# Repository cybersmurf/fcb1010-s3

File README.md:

# FCB1010-S3

Upgrade old fcb1010 to new era.

Přestavba nožního MIDI ovladače Behringer FCB1010 na ESP32-S3: původní hlavní deska a síťový zdroj ven, místo nich vlastní nosná deska s ESP32-S3-DevKitC-1.

*Rebuild of the Behringer FCB1010 MIDI foot controller around an ESP32-S3 (USB MIDI, 5-pin DIN MIDI, device profiles). Documentation is in Czech.*

## Co má umět

- **Ovladač DAW přes USB** (Logic Pro): transport, undo, cycle, metronom, pedály. USB MIDI bez ovladačů, napájení jedním kabelem USB-C.
- **Samostatný ovladač přes 5pinové MIDI**, hlavně pro Boss GX-700: volba patchů, pedály.
- **MIDI rozhraní USB ↔ DIN** pro počítač.
- Profily jako sestavy: jeden pedál může poslat více zpráv více přístrojům.
- Možnosti dalšího rozvoje: NUX MG-30 (jack TRS, USB host), Mackie Control s LED zpětnou vazbou, další profily.

## Stav (16. 11. 2026)

| Část | Stav |
|---|---|
| Koncepce a specifikace | hotová, verze 2 |
| Pinout a bloky nosné desky | verze 0.2, konektory předních desek neověřené |
| Firmware | verze 0.1: USB MIDI, 12 spínačů, 2 pedály, WS2812B. Sestaví se, **na hardwaru zatím neběžel** |
| Automatické kontroly | u každého pull requestu se pustí testy logiky a sestaví firmware |
| Měření vlastního kusu | čeká na otevření přístroje |
| Schéma a deska (KiCad) | nezačato |

## Obsah

| Cesta | Co tam je |
|---|---|
| [`docs/specifikace.md`](docs/specifikace.md) | co má přístroj umět, profily, směrování MIDI, stavba firmwaru, postup, rizika |
| [`docs/pinout.md`](docs/pinout.md) | přiřazení GPIO, konektory, bloky desky, displej |
| [`docs/obvody.md`](docs/obvody.md) | zapojení vstupů pedálů a spínačů, filtry, napájení, zem |
| [`docs/mereni.md`](docs/mereni.md) | měřicí protokol pro otevření přístroje |
| [`docs/nalezy-z-fotek.md`](docs/nalezy-z-fotek.md) | co je vidět na fotkách otevřeného přístroje (18. 11. 2026) |
| [`hardware/`](hardware/) | rozvržení nosné desky, schéma v PDF a [`hardware/kicad/`](hardware/kicad/) se schématem pro KiCad |
| [`docs/nakup.md`](docs/nakup.md) | nákupní seznam |
| [`docs/navrh.md`](docs/navrh.md) | první verze návrhu, co víme o vnitřku FCB, checklist měření |
| [`docs/pruzkum-vnitrni-zapojeni.md`](docs/pruzkum-vnitrni-zapojeni.md) | průzkum vnitřního zapojení FCB1010 s citacemi a mírou jistoty |
| [`docs/zdroje.md`](docs/zdroje.md) | všechny použité zdroje s výtahy |
| [`firmware/`](firmware/) | projekt pro PlatformIO (arduino-esp32 3.x) |

## Sestavení firmwaru

```
cd firmware
pio run
pio run -t upload
```

Podrobnosti v [`firmware/README.md`](firmware/README.md).

## Upozornění

- Uvnitř původního FCB1010 je síťové napětí. Měření za chodu jen s rozmyslem.
- Pinouty konektorů v dokumentaci pocházejí z cizích kusů a z fór. Před zapojením ověřit na vlastním přístroji.
- Licence zatím není určená.

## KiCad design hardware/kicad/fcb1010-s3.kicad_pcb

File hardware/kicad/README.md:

# Schéma nosné desky (KiCad)

| Soubor | Co to je |
|---|---|
| `fcb1010-s3.kicad_sch`, `fcb1010-s3.kicad_pro` | schéma, otevře se v KiCadu 7 a novějším |
| `gen_sch.py` | generátor schématu; zapojení je popsané v něm a schéma se z něj vyrábí |
| `expected-nets.json` | zamýšlené přiřazení pin → síť, vzniká při generování |
| `check_netlist.py` | porovná netlist vyexportovaný KiCadem se zamýšleným zapojením |
| `../schema-fcb1010-s3.pdf` | schéma v PDF |
| `gen_pcb.py` | generátor desky: rozmístění součástek a sítě; spouští se `/usr/bin/python3 gen_pcb.py` (potřebuje modul `pcbnew` z KiCadu) |
| `fcb1010-s3.kicad_pcb` | deska 229 × 41 mm, dvouvrstvá, součástky rozmístěné a spoje natažené autorouterem |
| `import_ses.py` | načte výsledek autorouteru Freerouting (`.ses`) do desky |
| `check_pcb.py` | nezávislá kontrola, že jsou v každé síti všechny pájecí body propojené |
| `../deska-fcb1010-s3.pdf`, `../deska-horni-strana.png`, `../deska-spodni-strana.png` | deska se spoji a obrázky obou stran |
| `../fcb1010-s3-gerber-v0.3.zip` | gerbery a vrtání pro výrobu |
| `fcb1010.pretty/` | vlastní pouzdra: DevKit 2×22 a úhelník |
| `parts.json` | seznam součástek (hodnota, pouzdro), vzniká při generování schématu |
| `../deska-rozmisteni.png` | obrázek rozmístění |

Postup po změně zapojení:

```
python3 gen_sch.py
kicad-cli sch export netlist -o fcb1010-s3.net fcb1010-s3.kicad_sch
python3 check_netlist.py fcb1010-s3.net
kicad-cli sch export pdf -o ../schema-fcb1010-s3.pdf fcb1010-s3.kicad_sch
```

Schéma se neupravuje ručně v editoru, jinak ho další generování přepíše.

## Stav (v0.1, 18. 11. 2026)

- Kontrola netlistu: 310 pinů, 90 sítí, bez rozdílů proti zadání.
- **Ověřeno z fotek (24. 11. 2026):** zapojení 14pinových svazků J1 a J2 (společný vodič, UP/DOWN, krajní spínač, napájení LED; pořadí prostředních pinů jednotlivě ne, dá se přemapovat ve firmwaru), rozložení pinů DevKitu a rozteč jeho řad 25,4 mm. Viz `docs/nalezy-z-fotek.md`.
- Orientace diod u spínačů: z fotek vychází společný vodič na GND a pull-up, tedy JP1 i JP2 v poloze A; při oživení ověřit.
- **Neověřeno:** pořadí vodičů pedálů J3 a J4, pořadí pinů modulu OLED (J5).
- Propojky JP1 a JP2 dovolují obrátit polaritu čtení spínačů, kdyby diody na předních deskách byly orientované opačně.
- U4 (MCP1702-4002E/TO, 4,0 V) je volitelný; bez něj se spojí JP3 a senzory pedálů se napájejí z 5 V přes R24 a C5.
- Deska: součástky jsou rozmístěné bez překryvů (kontrola v `gen_pcb.py`). Spoje natáhl Freerouting 1.9.0: 1326 segmentů, 61 prokovů, 7,5 m spojů. Signály 0,3 mm, GND a +5 V 0,6 mm, +3V3 a napájení senzorů 0,4 mm (s 0,6 mm se nedalo natáhnout). Izolační mezera 0,2 mm, spoje nejméně 0,6 mm od hrany desky. Na obou vrstvách je rozlitá zem.
- Kontroly (24. 11. 2026): KiCad i `check_pcb.py` hlásí 0 nepropojených spojení (90 sítí). Kontrola návrhových pravidel KiCadu (`drc.rpt`, pouští ji `import_ses.py`) nenašla žádný zkrat, porušení izolační mezery ani vzdálenosti od hrany. Zbývají jen upozornění: překryvy potisku, 2 zemní body připojených k rozlité zemi jedním můstkem místo dvou (jsou připojené i spojem).
- Konektory svazků J1 až J4 mají pin 1 (červený vodič) na konci dál od displeje, stejně jako původní deska (fotka IMG_9456). J1 je blíž k displeji a patří ke spodní desce spínačů (1–5, DOWN), J2 k horní (6–10, UP), viz `docs/nalezy-z-fotek.md`.
- Popisky konektorů jsou na potisku.
- Výrobní podklady: `../fcb1010-s3-gerber-v0.3.zip` (gerbery a vrtání, 2 vrstvy, 229 × 41 mm, tloušťka 1,6 mm). Oválné otvory úhelníků jsou prokovené drážky 1,3 × 2,1 mm.
- Polohy konektorů na hraně jsou podle fotek strany součástek s metrem zaháknutým za hranu desky (24. 11. 2026): pin 1 konektoru J1 na 40,3 mm, J2 74,3 mm, J4 89,0 mm, J3 100,5 mm, J7 (X18) 137,0 mm, J11 (X17) 210,3 mm od hrany u displeje; přesnost asi ±2 mm, u X17 a X18 ±3 mm. Lišty X17 a X18 mají rozteč 2,0 mm, J7 a J11 jsou proto obyčejné řady 1×4 s roztečí 2,0 mm, do kterých se dají přepájet původní lišty s límcem. Pin 1 (červený vodič) je u všech na konci dál od displeje; u X17 a X18 je to odvozené z potisku a ostatních konektorů, při pájení ověřit podle červeného vodiče.
- **Pod DevKitem není žádná součástka (v0.3, 24. 11. 2026).** JP1 a JP2 jsou nad budičem U3, JP3 u stabilizátoru senzorů, JP4 a J9 na konci desky u výstupů, odpory R18 až R23 a kondenzátory C3, C4 ve dvou řadách mezi DevKitem a hranou se svazky. Kontrola v `gen_pcb.py` hlídá i překryv s DevKitem.
- Displej na desce není: připojuje se čtyřpinovým konektorem J5 a jeho držák se vyřeší podle skutečného modulu.
- Deska je připravená k objednání prototypu. Zbylé neověřené body se dají vyřešit při osazování (pořadí vodičů při pájení, propojky, firmware).

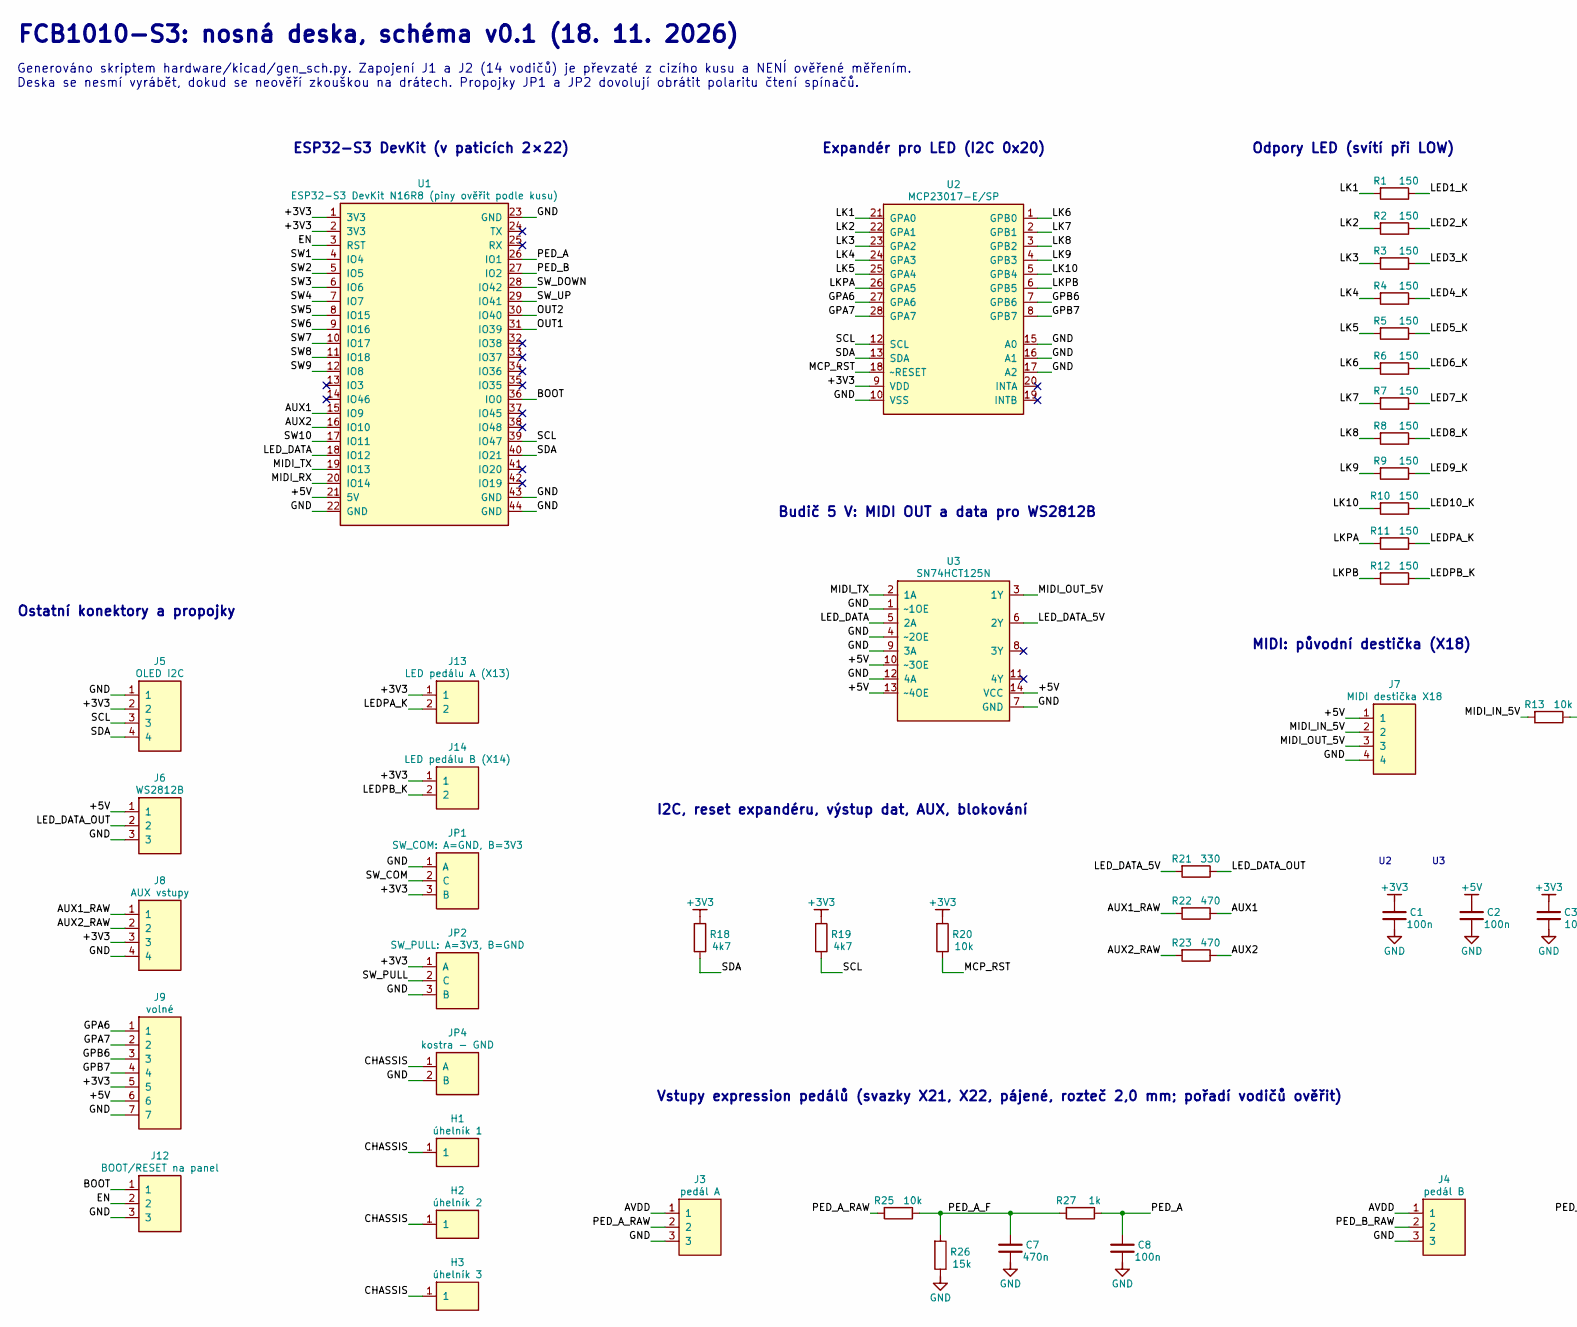
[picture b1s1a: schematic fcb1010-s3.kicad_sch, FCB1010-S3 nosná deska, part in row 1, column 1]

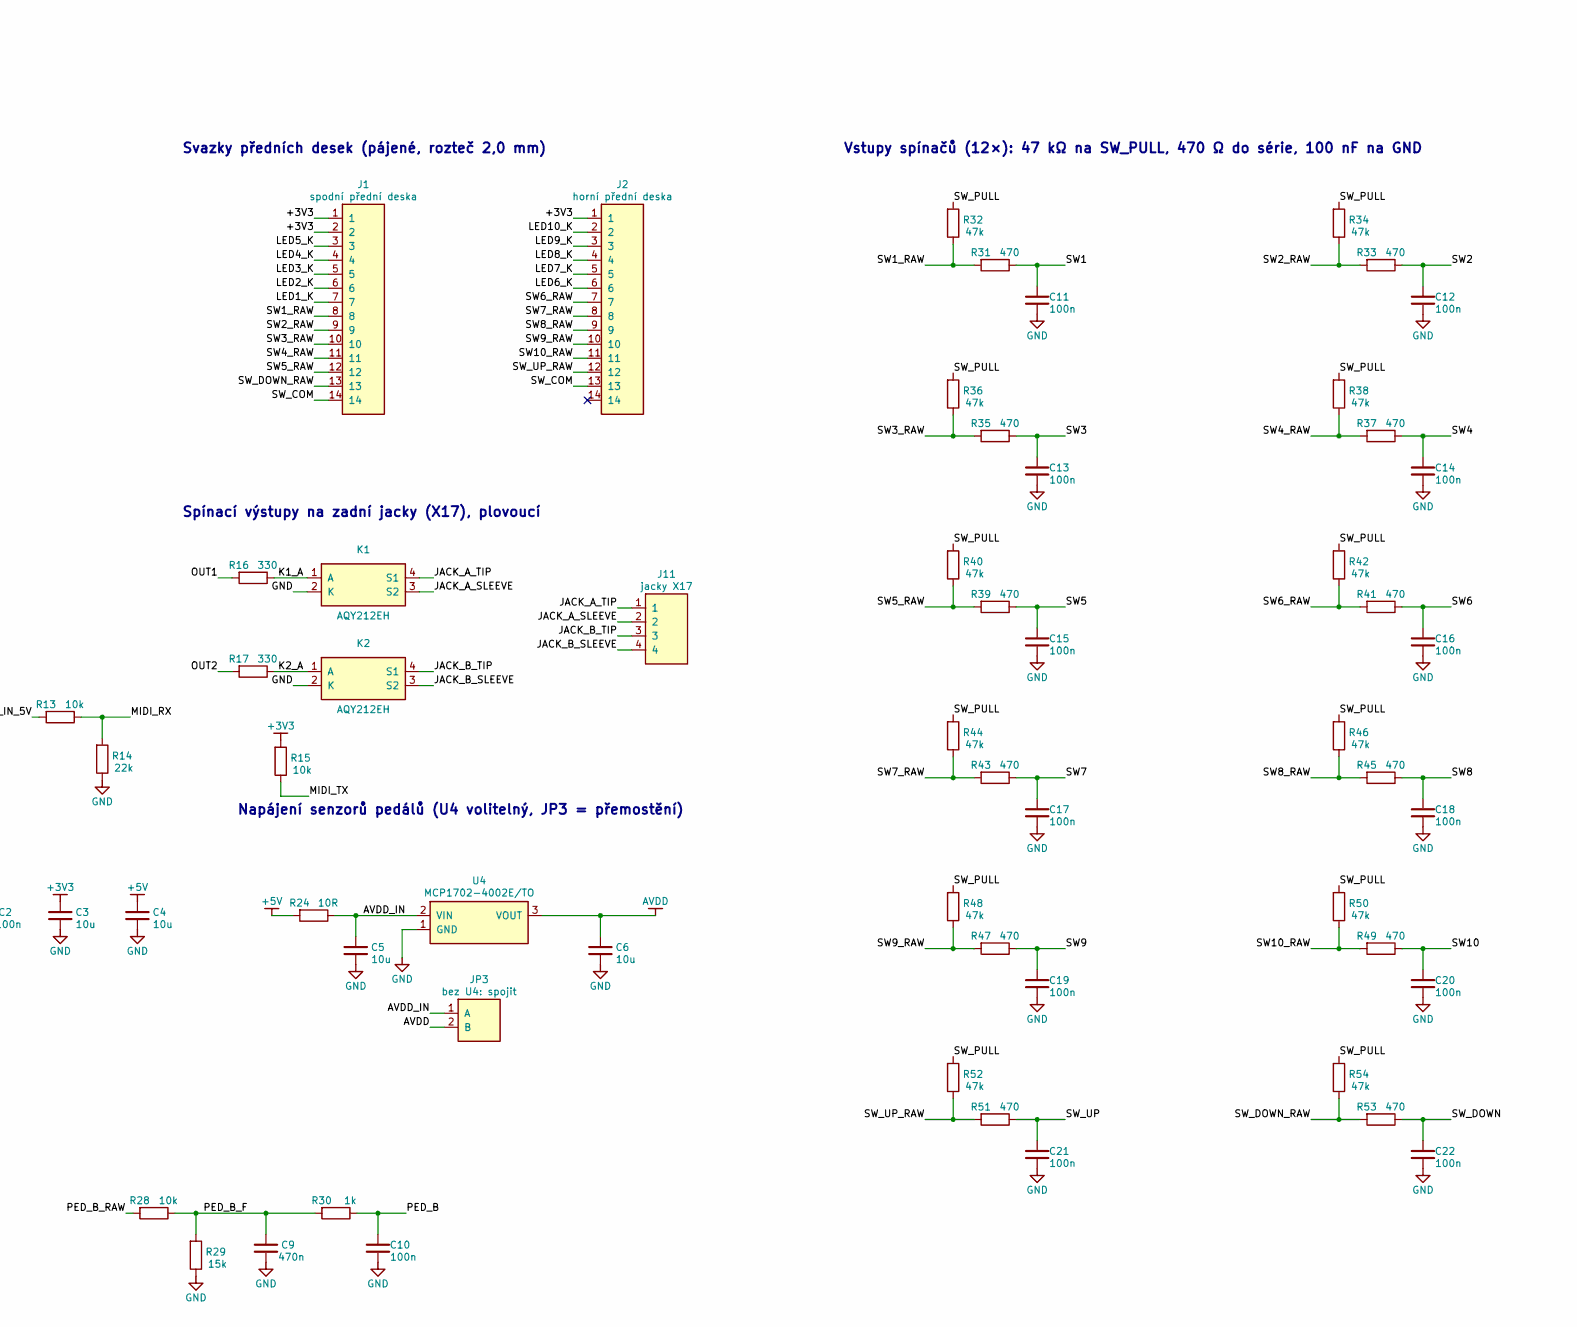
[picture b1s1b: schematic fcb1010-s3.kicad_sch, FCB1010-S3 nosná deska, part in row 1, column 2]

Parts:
C1, C2, C8, C10, C11, C12, C13, C14, C15, C16, C17, C18, C19, C20, C21, C22: 100n; C_Disc_D5.0mm_W2.5mm_P5.00mm
C3, C4, C5, C6: 10u; C_Disc_D5.0mm_W2.5mm_P5.00mm
C7, C9: 470n; C_Disc_D5.0mm_W2.5mm_P5.00mm
H1: úhelník 1; Uhelnik
H2: úhelník 2; Uhelnik
H3: úhelník 3; Uhelnik
J1: spodní přední deska; PinHeader_1x14_P2.00mm_Vertical
J2: horní přední deska; PinHeader_1x14_P2.00mm_Vertical
J3: pedál A; PinHeader_1x03_P2.00mm_Vertical
J4: pedál B; PinHeader_1x03_P2.00mm_Vertical
J5: OLED I2C; PinHeader_1x04_P2.54mm_Vertical
J6: WS2812B; PinHeader_1x03_P2.54mm_Vertical
J7: MIDI destička X18; PinHeader_1x04_P2.00mm_Vertical
J8: AUX vstupy; PinHeader_1x04_P2.54mm_Vertical
J9: volné; PinHeader_1x07_P2.54mm_Vertical
J11: jacky X17; PinHeader_1x04_P2.00mm_Vertical
J12: BOOT/RESET na panel; PinHeader_1x03_P2.54mm_Vertical
J13: LED pedálu A (X13); PinHeader_1x02_P2.00mm_Vertical
J14: LED pedálu B (X14); PinHeader_1x02_P2.00mm_Vertical
JP1: SW_COM: A=GND, B=3V3; PinHeader_1x03_P2.54mm_Vertical
JP2: SW_PULL: A=3V3, B=GND; PinHeader_1x03_P2.54mm_Vertical
JP3: bez U4: spojit; PinHeader_1x02_P2.54mm_Vertical
JP4: kostra - GND; PinHeader_1x02_P2.54mm_Vertical
K1, K2: AQY212EH; DIP-4_W7.62mm
R1, R2, R3, R4, R5, R6, R7, R8, R9, R10, R11, R12: 150; R_Axial_DIN0207_L6.3mm_D2.5mm_P10.16mm_Horizontal
R13, R15, R20, R25, R28: 10k; R_Axial_DIN0207_L6.3mm_D2.5mm_P10.16mm_Horizontal
R14: 22k; R_Axial_DIN0207_L6.3mm_D2.5mm_P10.16mm_Horizontal
R16, R17, R21: 330; R_Axial_DIN0207_L6.3mm_D2.5mm_P10.16mm_Horizontal
R18, R19: 4k7; R_Axial_DIN0207_L6.3mm_D2.5mm_P10.16mm_Horizontal
R22, R23, R31, R33, R35, R37, R39, R41, R43, R45, R47, R49, R51, R53: 470; R_Axial_DIN0207_L6.3mm_D2.5mm_P10.16mm_Horizontal
R24: 10R; R_Axial_DIN0207_L6.3mm_D2.5mm_P10.16mm_Horizontal
R26, R29: 15k; R_Axial_DIN0207_L6.3mm_D2.5mm_P10.16mm_Horizontal
R27, R30: 1k; R_Axial_DIN0207_L6.3mm_D2.5mm_P10.16mm_Horizontal
R32, R34, R36, R38, R40, R42, R44, R46, R48, R50, R52, R54: 47k; R_Axial_DIN0207_L6.3mm_D2.5mm_P10.16mm_Horizontal
U1: ESP32-S3 DevKit N16R8 (piny ověřit podle kusu); ESP32-S3-DevKit_2x22_RM25.4mm
U2: MCP23017-E/SP; DIP-28_W7.62mm_Socket
U3: SN74HCT125N; DIP-14_W7.62mm_Socket
U4: MCP1702-4002E/TO; TO-92_Inline

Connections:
+3V3: C1.1, C3.1, J1.1, J1.2, J2.1, J5.2, J8.3, J9.5, J13.1, J14.1, JP1.3 (B), JP2.1 (A), R15.1, R18.1, R19.1, R20.1, U1.1 (3V3), U1.2 (3V3), U2.9 (VDD)
+5V: C2.1, C4.1, J6.1, J7.1, J9.6, R24.1, U1.21 (5V), U3.10 (~3OE), U3.13 (~4OE), U3.14 (VCC)
AUX1: R22.2, U1.15 (IO9)
AUX1_RAW: J8.1, R22.1
AUX2: R23.2, U1.16 (IO10)
AUX2_RAW: J8.2, R23.1
AVDD: C6.1, J3.1, J4.1, JP3.2 (B), U4.3 (VOUT)
AVDD_IN: C5.1, JP3.1 (A), R24.2, U4.2 (VIN)
BOOT: J12.1, U1.36 (IO0)
CHASSIS: H1.1, H2.1, H3.1, JP4.1 (A)
EN: J12.2, U1.3 (RST)
GND: C1.2, C2.2, C3.2, C4.2, C5.2, C6.2, C7.2, C8.2, C9.2, C10.2, C11.2, C12.2, C13.2, C14.2, C15.2, C16.2, C17.2, C18.2, C19.2, C20.2, C21.2, C22.2, J3.3, J4.3, J5.1, J6.3, J7.4, J8.4, J9.7, J12.3, JP1.1 (A), JP2.3 (B), JP4.2 (B), K1.2 (K), K2.2 (K), R14.2, R26.2, R29.2, U1.22 (GND), U1.23 (GND), U1.43 (GND), U1.44 (GND), U2.10 (VSS), U2.15 (A0), U2.16 (A1), U2.17 (A2), U3.1 (~1OE), U3.4 (~2OE), U3.7 (GND), U3.9 (3A), U3.12 (4A), U4.1 (GND)
GPA6: J9.1, U2.27 (GPA6)
GPA7: J9.2, U2.28 (GPA7)
GPB6: J9.3, U2.7 (GPB6)
GPB7: J9.4, U2.8 (GPB7)
JACK_A_SLEEVE: J11.2, K1.3 (S2)
JACK_A_TIP: J11.1, K1.4 (S1)
JACK_B_SLEEVE: J11.4, K2.3 (S2)
JACK_B_TIP: J11.3, K2.4 (S1)
K1_A: K1.1 (A), R16.2
K2_A: K2.1 (A), R17.2
LED1_K: J1.7, R1.2
LED2_K: J1.6, R2.2
LED3_K: J1.5, R3.2
LED4_K: J1.4, R4.2
LED5_K: J1.3, R5.2
LED6_K: J2.6, R6.2
LED7_K: J2.5, R7.2
LED8_K: J2.4, R8.2
LED9_K: J2.3, R9.2
LED10_K: J2.2, R10.2
LEDPA_K: J13.2, R11.2
LEDPB_K: J14.2, R12.2
LED_DATA: U1.18 (IO12), U3.5 (2A)
LED_DATA_5V: R21.1, U3.6 (2Y)
LED_DATA_OUT: J6.2, R21.2
LK1: R1.1, U2.21 (GPA0)
LK2: R2.1, U2.22 (GPA1)
LK3: R3.1, U2.23 (GPA2)
LK4: R4.1, U2.24 (GPA3)
LK5: R5.1, U2.25 (GPA4)
LK6: R6.1, U2.1 (GPB0)
LK7: R7.1, U2.2 (GPB1)
LK8: R8.1, U2.3 (GPB2)
LK9: R9.1, U2.4 (GPB3)
LK10: R10.1, U2.5 (GPB4)
LKPA: R11.1, U2.26 (GPA5)
LKPB: R12.1, U2.6 (GPB5)
MCP_RST: R20.2, U2.18 (~RESET)
MIDI_IN_5V: J7.2, R13.1
MIDI_OUT_5V: J7.3, U3.3 (1Y)
MIDI_RX: R13.2, R14.1, U1.20 (IO14)
MIDI_TX: R15.2, U1.19 (IO13), U3.2 (1A)
OUT1: R16.1, U1.31 (IO39)
OUT2: R17.1, U1.30 (IO40)
PED_A: C8.1, R27.2, U1.26 (IO1)
PED_A_F: C7.1, R25.2, R26.1, R27.1
PED_A_RAW: J3.2, R25.1
PED_B: C10.1, R30.2, U1.27 (IO2)
PED_B_F: C9.1, R28.2, R29.1, R30.1
PED_B_RAW: J4.2, R28.1
SCL: J5.3, R19.2, U1.39 (IO47), U2.12 (SCL)
SDA: J5.4, R18.2, U1.40 (IO21), U2.13 (SDA)
SW1: C11.1, R31.2, U1.4 (IO4)
SW1_RAW: J1.8, R31.1, R32.2
SW2: C12.1, R33.2, U1.5 (IO5)
SW2_RAW: J1.9, R33.1, R34.2
SW3: C13.1, R35.2, U1.6 (IO6)
SW3_RAW: J1.10, R35.1, R36.2
SW4: C14.1, R37.2, U1.7 (IO7)
SW4_RAW: J1.11, R37.1, R38.2
SW5: C15.1, R39.2, U1.8 (IO15)
SW5_RAW: J1.12, R39.1, R40.2
SW6: C16.1, R41.2, U1.9 (IO16)
SW6_RAW: J2.7, R41.1, R42.2
SW7: C17.1, R43.2, U1.10 (IO17)
SW7_RAW: J2.8, R43.1, R44.2
SW8: C18.1, R45.2, U1.11 (IO18)
SW8_RAW: J2.9, R45.1, R46.2
SW9: C19.1, R47.2, U1.12 (IO8)
SW9_RAW: J2.10, R47.1, R48.2
SW10: C20.1, R49.2, U1.17 (IO11)
SW10_RAW: J2.11, R49.1, R50.2
SW_COM: J1.14, J2.13, JP1.2 (C)
SW_DOWN: C22.1, R53.2, U1.28 (IO42)
SW_DOWN_RAW: J1.13, R53.1, R54.2
SW_PULL: JP2.2 (C), R32.1, R34.1, R36.1, R38.1, R40.1, R42.1, R44.1, R46.1, R48.1, R50.1, R52.1, R54.1
SW_UP: C21.1, R51.2, U1.29 (IO41)
SW_UP_RAW: J2.12, R51.1, R52.2

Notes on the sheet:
FCB1010-S3: nosná deska, schéma v0.1 (18. 11. 2026)
Generováno skriptem hardware/kicad/gen_sch.py. Zapojení J1 a J2 (14 vodičů) je převzaté z cizího kusu a NENÍ ověřené měřením. Deska se nesmí vyrábět, dokud se neověří zkouškou na drátech. Propojky JP1 a JP2 dovolují obrátit polaritu čtení spínačů.
ESP32-S3 DevKit (v paticích 2×22)
Expandér pro LED (I2C 0x20)
Odpory LED (svítí při LOW)
Svazky předních desek (pájené, rozteč 2,0 mm)
Budič 5 V: MIDI OUT a data pro WS2812B
MIDI: původní destička (X18)
Spínací výstupy na zadní jacky (X17), plovoucí
Ostatní konektory a propojky
I2C, reset expandéru, výstup dat, AUX, blokování
U2 U3
Napájení senzorů pedálů (U4 volitelný, JP3 = přemostění)
Vstupy expression pedálů (svazky X21, X22, pájené, rozteč 2,0 mm; pořadí vodičů ověřit)
Vstupy spínačů (12×): 47 kΩ na SW_PULL, 470 Ω do série, 100 nF na GND

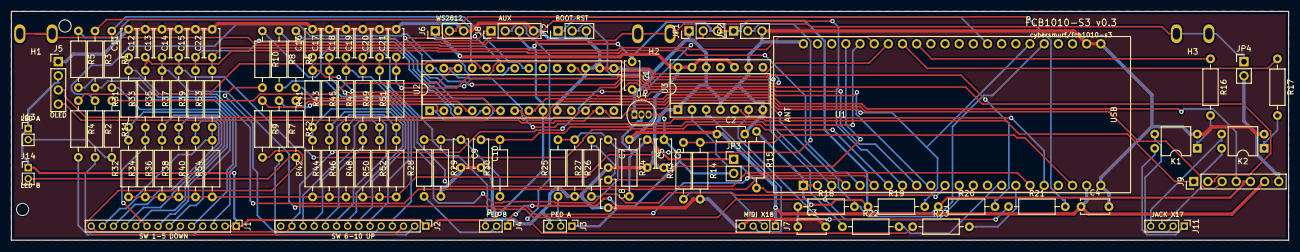
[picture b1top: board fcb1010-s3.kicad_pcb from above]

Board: 2 copper layers, 229.0 x 41.0 mm, 104 parts (0 on the bottom side), 90 nets.

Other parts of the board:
MH1, MH2: MountingHole_2.2mm_M2

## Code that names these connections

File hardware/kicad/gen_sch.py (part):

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
SW_GPIO = [4, 5, 6, 7, 15, 16, 17, 18, 8, 11]          # spínače 1 až 10
gpio_net = {f"IO{g}": f"SW{i + 1}" for i, g in enumerate(SW_GPIO)}
gpio_net.update({"IO41": "SW_UP", "IO42": "SW_DOWN", "IO1": "PED_A", "IO2": "PED_B", "IO9": "AUX1", "IO10": "AUX2",
                 "IO12": "LED_DATA", "IO13": "MIDI_TX", "IO14": "MIDI_RX", "IO21": "SDA", "IO47": "SCL",
                 "IO39": "OUT1", "IO40": "OUT2", "IO0": "BOOT", "RST": "EN", "3V3": "+3V3", "5V": "+5V", "GND": "GND"})

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         {"1": "+5V", "2": "MIDI_IN_5V", "3": "MIDI_OUT_5V", "4": "GND"})
# dělič MIDI IN
x, y = 290, 136
label("MIDI_IN_5V", (x - 5.08, y), "L")
ref, p = R_h(x, y, "10k", "MIDI_IN_5V", "MIDI_RX")
wire((x - 5.08, y), p["1"])
b = (x + 7.62, y)
wire(p["2"], b, (x + 12.7, y)); label("MIDI_RX", (x + 12.7, y), "R"); junction(b)
ref, p = R_v(b[0], y + 7.62, "22k", "MIDI_RX", "GND")
wire(b, p["1"]); pwr("GND", p["2"])
# pull-up MIDI_TX (klid = log. 1, proud smyčkou neteče ani při startu)
x, y = 330, 144
ref, p = R_v(x, y, "10k", "+3V3", "MIDI_TX")
pwr("+3V3", p["1"])
wire(p["2"], (x, y + 6.35), (x + 5.08, y + 6.35)); label("MIDI_TX", (x + 5.08, y + 6.35), "R")

# ---- spínací výstupy
text("Spínací výstupy na zadní jacky (X17), plovoucí", 312, 100, 1.8, True)
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ref, p = R_h(x, y, "10R", "+5V", "AVDD_IN")
wire(p["1"], (x - 7.62, y)); pwr("+5V", (x - 7.62, y))
n1 = (x + 7.62, y)
wire(p["2"], n1); junction(n1); label("AVDD_IN", (n1[0] + 1.27, y), "R")
ref, c = C_v(n1[0], y + 6.35, "10u", "AVDD_IN", "GND"); wire(n1, c["1"]); pwr("GND", c["2"])
u = place("fcb:MCP1702-4002", 366, y + 1.27, "U4", "MCP1702-4002E/TO", "Package_TO_SOT_THT:TO-92_Inline",
          {"2": "AVDD_IN", "1": "GND", "3": "AVDD"}, ref_at=(0, -7.6), val_at=(0, -5.4))
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    wire((x - 5.08, y), a, p["1"]); junction(a)
    ref, r = R_v(x, y - 7.62, "47k", "SW_PULL", f"{nm}_RAW")
    wire(a, r["2"])
    label("SW_PULL", (x, r["1"][1]), "R")
    b = (x + 15.24, y)
    wire(p["2"], b, (x + 20.32, y)); junction(b); label(nm, (x + 20.32, y), "R")
    ref, c = C_v(b[0], y + 6.35, "100n", nm, "GND"); wire(b, c["1"]); pwr("GND", c["2"])
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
